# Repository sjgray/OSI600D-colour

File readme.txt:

Ohio Scientific Superboard 600D Colour board
============================================

The Superboard-II Revision D (600D from now on) was designed for colour expansion. The motherboard includes a socket for
one extra 2114 "colour ram" and the U75 dip connector. Plugging in a new 2114 and running a ribbon cable to the 630 board
would enable the colour. Unfortunate the 630 board is (afaik) very rare, and there is no reproduction available. However,
with signals coming from U75 we are able to tap into the colour data and make our own system. U75 contains the sync, video,
and control signals we need, along with 4 lines for colour data. I decided it would be easy to use the /SVID signal (after
being inverted) to select between the colour lines for ON pixels and black for OFF pixels. Using a simple 74LS157 quad
multiplexer toggled by the SVID signal.

The 600D boots up in monochrome mode and has no firmware support for colour, so we would get random colours every time and
the screen would be hard to read. I added a second multiplexer for monochrome mode. The video signal is routed through a DIP
switch to one of the MUX inputs so you can select the "colour" of your monochrome "tube", and the output from the first MUX
goes to the 2nd MUX's other input. The U75 COLOR_EN line controls this MUX. When colour is enabled the SVID line output feeds
the proper inputs setting them ON when SVID is high producing the selected colour, or OFF when SVID is LOW, producing black.

The four colour bits represent the Red, Green, and Blue colour components plus one Intensity component. This is known as RGBI
and was used in IBM's CGA video board. RGBI is a digital system. With 4 bits it can generate 8 basic colours (including black)
and 8 more brighter versions of those colours (black becomes grey). Most modern monitors can not handle CGA signals but some
can handle RGB signals. To convert from RGBI to RGB the output of the second mux is passed through a DAC consisting of resistors
and diodes. This also reduces the voltage levels for the monitor. That, along with the proper sync for your monitor lets the
OSI produce 16 glorious colours!

Board Features
--------------

The board mounts on the U75 socket and has holes for stand-offs to hold it up. There are jumpers to select the polarity of
the sync signals (composite, horizontal, vertical) that are sent to the output headers. There is a 10-pin RGBS header and
a 5-pin Gonbes header

The RGBS Header can be used to attach a DB-9 connector via an IDC ribbon cable or to a SCART adapter via custom wiring.
You can select RGBS (composite sync) or RGBHV (separate sync) by the appropriate sync header jumpers. Each sync signal can
be normal or inverted. You should have a single jumper for composite sync or two jumpers (H and V) for separate sync.
If using SCART you should use composite sync and should populate resistor R5, and connect PIN10 on the header to the SCART
mode select pin and it will select RGB mode automatically.

The Gonbes header can be uses to connect a GB-82xx adapter. It uses composite sync only, so jumper the CS pin. The input
on the Gonbes adapter requires a reduced voltage on the composite sync which is handled by resistor R9.

The 600D boots in monochrome mode and a control register must be used to enable colour. When in monochrome mode it will
display all characters in the color selected by the DIP switch, so for example you could set the switches to all ON for
white, or just the G switch for green. The I switch makes the colour brighter. When colour is enabled on the register
the 4 bit data from the colour RAM are used instead.

The resulting RGBI digital signal is sent to a resistor DAC and converted to analog RGB.

Firmware
--------

You can use the 600D firmware as-is and write your own software to set the control register and draw to the screen
directly. I'm not aware of any original OSI software that works in colour with 600D as the OSI colour board was very rare.
The OSI C4P used colour but had a different screen format and memory mapping so it would be possible to convert C4P
software to the 600D.

You can also use modified firmware such as my "SJGMON" ROM, which is a modified CEGMON ROM to support the 600D features.
It will allow you to use control codes to turn colour on or off and to set the screen mode (24x24 or 48x16). The only
drawback is SJGMON replaces the DISK BOOT code with the 600D colour code.

Hardware Installation
---------------------

The board is installed onto the U75 IC socket, however you must make a small modification on the 600D motherboard to
enable colour. You must cut one trace and install a wire jumper. In the PICS directory are picture that show the
modifications that are required.

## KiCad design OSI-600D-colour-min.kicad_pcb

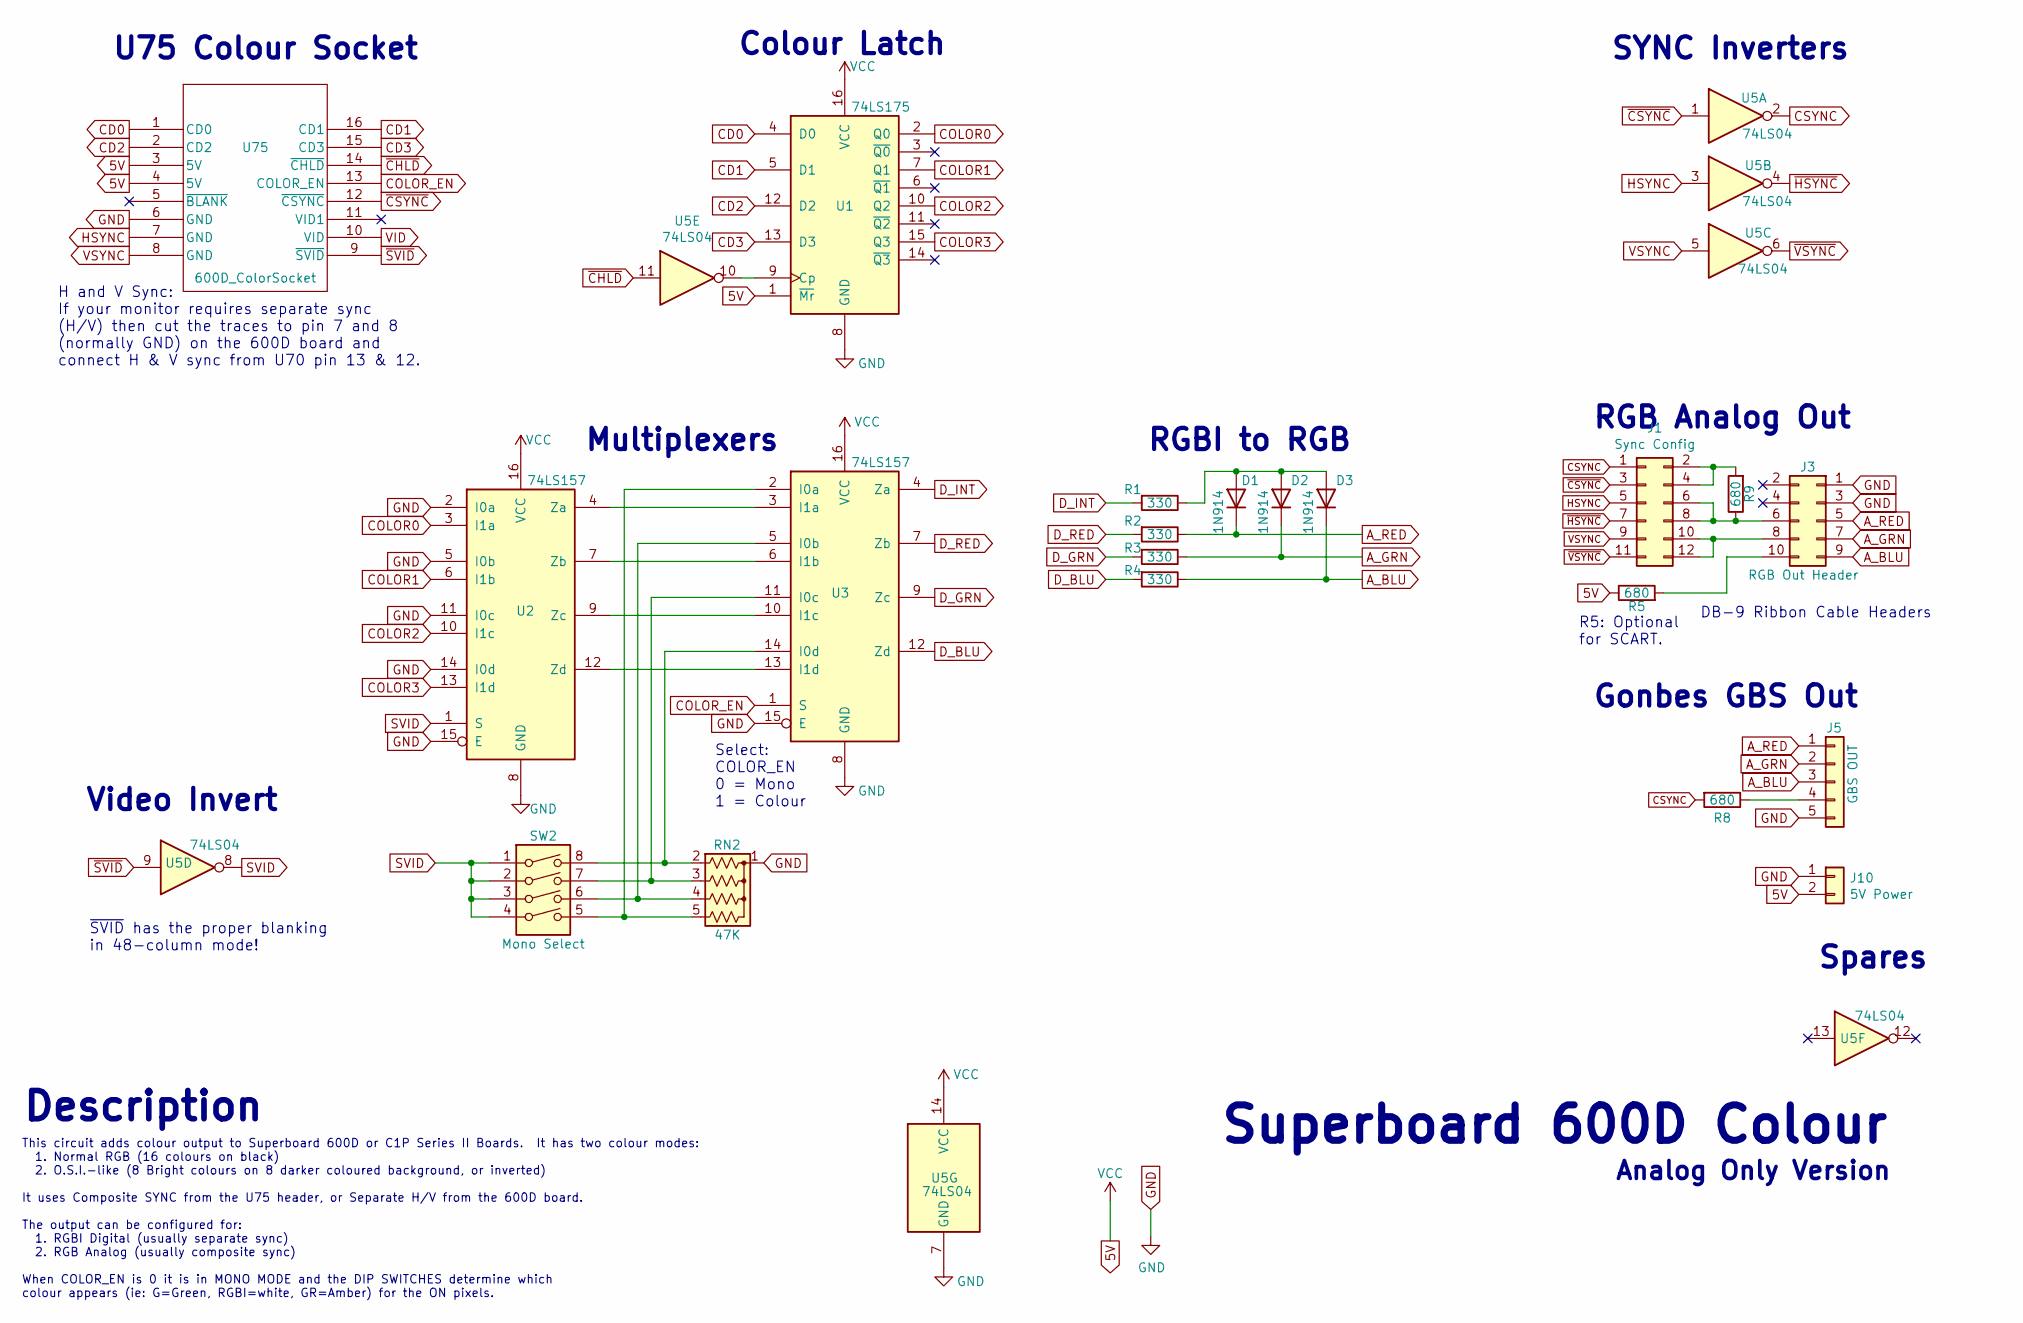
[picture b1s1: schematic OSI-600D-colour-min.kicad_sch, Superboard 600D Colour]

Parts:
D1, D2, D3: 1N914; D_DO-34_SOD68_P7.62mm_Horizontal
J1: Sync Config; PinHeader_2x06_P2.54mm_Vertical
J3: RGB Out Header; PinHeader_2x05_P2.54mm_Vertical
J5: GBS OUT; PinHeader_1x05_P2.54mm_Vertical
J10: 5V Power; PinHeader_1x02_P2.54mm_Vertical
R1, R2, R3, R4: 330; R_Axial_DIN0204_L3.6mm_D1.6mm_P7.62mm_Horizontal
R5, R8, R9: 680; R_Axial_DIN0204_L3.6mm_D1.6mm_P7.62mm_Horizontal
RN2: 47K; R_Array_SIP5
SW2: Mono Select; SW_DIP_SPSTx04_Slide_6.7x11.72mm_W7.62mm_P2.54mm_LowProfile
U1: 74LS175; DIP-16_W7.62mm_LongPads
U2, U3: 74LS157; DIP-16_W7.62mm_LongPads
U5: 74LS04; DIP-14_W7.62mm_LongPads
U75: 600D_ColorSocket; DIP-16_W7.62mm_Socket_LongPads

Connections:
5V: J10.2, R5.1, U1.1 (~Mr), U1.16 (VCC), U2.16 (VCC), U3.16 (VCC), U5.14 (VCC), U75.3 (5V), U75.4 (5V)
A_BLU: D3.1 (K), J3.9, J5.3, R4.1
A_GRN: D2.1 (K), J3.7, J5.2, R3.1
A_RED: D1.1 (K), J3.5, J5.1, R2.1
CD0: U1.4 (D0), U75.1 (CD0)
CD1: U1.5 (D1), U75.16 (CD1)
CD2: U1.12 (D2), U75.2 (CD2)
CD3: U1.13 (D3), U75.15 (CD3)
COLOR0: U1.2 (Q0), U2.3 (I1a)
COLOR1: U1.7 (Q1), U2.6 (I1b)
COLOR2: U1.10 (Q2), U2.10 (I1c)
COLOR3: U1.15 (Q3), U2.13 (I1d)
COLOR_EN: U3.1 (S), U75.13 (COLOR_EN)
CSYNC: J1.1, R8.2, U5.2
D_BLU: R4.2, U3.12 (Zd)
D_GRN: R3.2, U3.9 (Zc)
D_INT: R1.2, U3.4 (Za)
D_RED: R2.2, U3.7 (Zb)
GND: J3.1, J3.3, J5.5, J10.1, RN2.1 (common), U1.8 (GND), U2.2 (I0a), U2.5 (I0b), U2.8 (GND), U2.11 (I0c), U2.14 (I0d), U2.15 (E), U3.8 (GND), U3.15 (E), U5.7 (GND), U75.6 (GND)
HSYNC: J1.5, U5.3, U75.7 (GND)
unnamed: D1.2 (A), D2.2 (A), D3.2 (A), R1.1
unnamed: J1.2, J1.4, R9.2
unnamed: J1.6, J1.8, J3.6, R9.1
unnamed: J1.10, J1.12, J3.8
unnamed: J3.10, R5.2
unnamed: J5.4, R8.1
unnamed: RN2.2 (R1), SW2.8, U3.14 (I0d)
unnamed: RN2.3 (R2), SW2.7, U3.11 (I0c)
unnamed: RN2.4 (R3), SW2.6, U3.5 (I0b)
unnamed: RN2.5 (R4), SW2.5, U3.2 (I0a)
unnamed: U1.9 (Cp), U5.10
unnamed: U2.4 (Za), U3.3 (I1a)
unnamed: U2.7 (Zb), U3.6 (I1b)
unnamed: U2.9 (Zc), U3.10 (I1c)
unnamed: U2.12 (Zd), U3.13 (I1d)
SVID: SW2.1, SW2.2, SW2.3, SW2.4, U2.1 (S), U5.8
VSYNC: J1.9, U5.5, U75.8 (GND)
~CHLD: U5.11, U75.14 (~CHLD)
~CSYNC: J1.3, U5.1, U75.12 (~CSYNC)
~HSYNC: J1.7, U5.4
~SVID: U5.9, U75.9 (~SVID)
~VSYNC: J1.11, U5.6

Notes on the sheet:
R5: Optional for SCART.
RGB Analog Out
Analog Only Version
Gonbes GBS Out
RGBI to RGB
U75 Colour Socket
H and V Sync: If your monitor requires separate sync (H/V) then cut the traces to pin 7 and 8 (normally GND) on the 600D board and connect H & V sync from U70 pin 13 & 12.
Superboard 600D Colour
Multiplexers
Colour Latch
Spares
~{SVID} has the proper blanking in 48-column mode!
SYNC Inverters
Description
DB-9 Ribbon Cable Headers
Select: COLOR_EN 0 = Mono 1 = Colour
This circuit adds colour output to Superboard 600D or C1P Series II Boards. It has two colour modes: 1. Normal RGB (16 colours on black) 2. O.S.I.-like (8 Bright colours on 8 darker coloured background, or inverted) It uses Composite SYNC from the U75 header, or Separate H/V from the 600D board. Th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
Video Invert

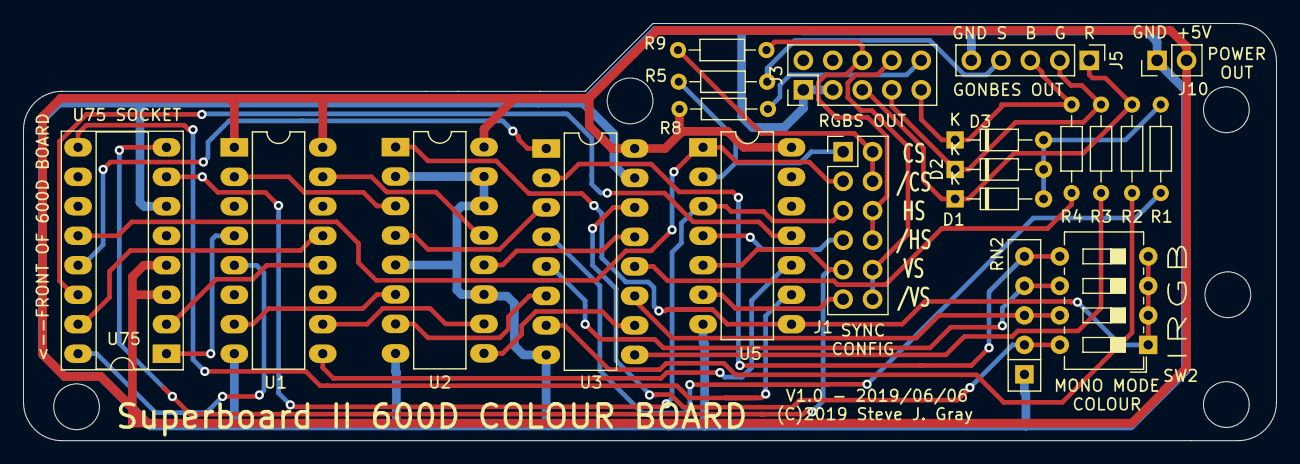
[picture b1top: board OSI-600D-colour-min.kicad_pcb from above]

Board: 2 copper layers, 107.9 x 35.9 mm, 21 parts (0 on the bottom side), 42 nets.

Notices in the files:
OSI-600D-colour-min.kicad_pcb:
(C)2019 Steve J. Gray
